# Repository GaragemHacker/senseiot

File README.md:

senseiot
========

.

Sense IoT é um projeto para pesquisa e desenvolvimento de uma rede de sensores sem fio.

Sensores
--------

* **ht**: Umidade e temperatura.
* **sound**: Som.
* **presence**: Presença.
* **gas**: Gás.
* **rain**: Chuva.

ESP8266
-------

Vamos utilizar o ESP8266 neste projeto.
Veja o wiki para uma introdução ao
[ESP8266](https://github.com/Garagem-Hacker/senseiot/wiki).

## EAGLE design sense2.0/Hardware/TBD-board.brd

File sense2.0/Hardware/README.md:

senseiot
========

Placas de Monitoramento de Consumo e Comando.

Schematic
-------
***CurrentMeasBoard**

***RelesBoard**

Board
-----

***CurrentMeasBoard**

***RelesBoard**

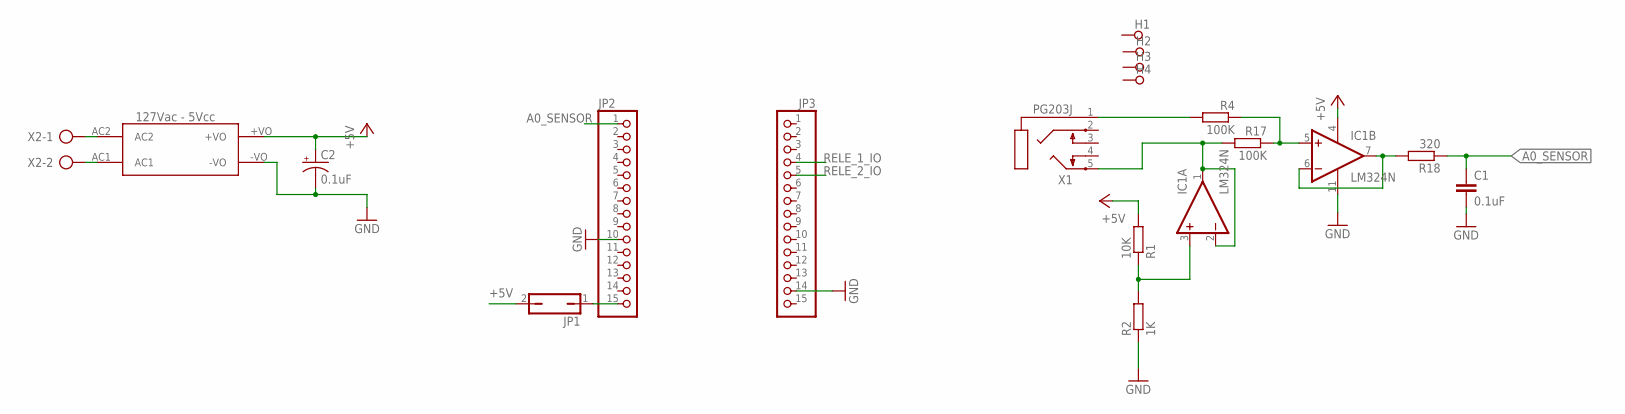
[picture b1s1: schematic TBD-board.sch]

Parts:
C1: 0.1uF; C5B5
C2: 0.1uF; E2,5-6
FONTE: HLK-PM01
H1, H2, H3, H4: SPECIAL_DRILL_0.1000; PAD_0.1000
IC1: LM324N; DIL14
JP1: JP1Q; JP1
JP2, JP3: PINHD-1X15; 1X15
R1: 10K; 0207/7
R2: 1K; 0207/7
R4, R17: 100K; 0207/7
R18: 320; 0207/7
X1: PG203J
X2: AK300/2

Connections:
+5V: C2.+, FONTE.+VO, IC1.4 (V+), JP1.2, R1.2
A0_SENSOR: C1.1, JP2.1, R18.1
GND: C1.2, C2.-, FONTE.-VO, IC1.11 (V-), JP2.10, JP3.14, R2.1
LOAD+: FONTE.AC2, X2.1
LOAD-: FONTE.AC1, X2.2
unnamed: IC1.3 (+IN), R1.1, R2.2
unnamed: JP1.1, JP2.15
unnamed: R4.2, X1.1
unnamed: IC1.5 (+IN), R4.1, R17.1
unnamed: IC1.6 (-IN), IC1.7 (OUT), R18.2
RELE_1_IO: JP3.4
RELE_2_IO: JP3.5
SENSOR-A-2: IC1.1 (OUT), IC1.2 (-IN), R17.2, X1.5

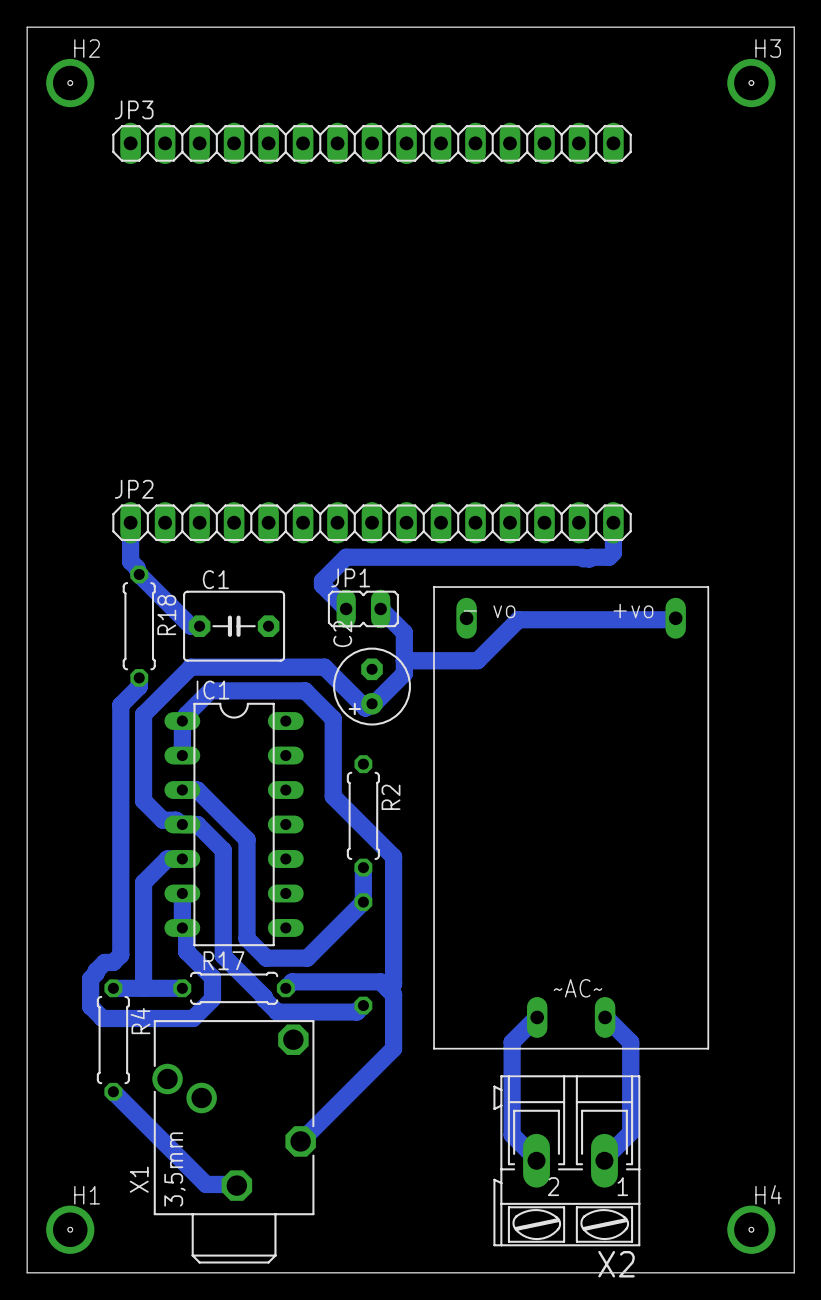
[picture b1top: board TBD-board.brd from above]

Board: 2 copper layers, 56.5 x 91.7 mm, 18 parts (1 on the bottom side), 11 nets.

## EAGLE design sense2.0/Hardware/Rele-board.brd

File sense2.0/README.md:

Senseiot 2.0
============
Nova Versão de Sense IoT

.

Sense IoT é um projeto para pesquisa e desenvolvimento de uma rede de sensores sem fio.

Hardware
--------
* **ESP8266**: Nó IoT;
* **Raspberry**: Gateway IoT;
* **ht05**: Sensor de Umidade e Temperatura;
* **sct**: Sensor de Corrente Elétrica;
* **ASQ/Ctrl-Board**: Aquisição de corrente e Comandos elétricos.
* NodeMCU: Nó Lora com sensores BMP085 e TSL2561.

Software
--------
* **API**: Da acesso do banco de dados ao Servidor Mathematica
* **Crypto**: Encript/Decrypt Payload
* **Docker**: Docker Containers
* **Mathematica**: Computer Algebra System (CAS) para Analytics dos dados
* **WebPage**: Visualização dos dados coletados e comandos para controle.

Ferramentas
-----------
* **BrokerMQTT**: Servidor IoT MQTT
* **Flask**: Microframework para aplicação Web
* **Docker**: Docker Containers
* **Crypto**: Rotinas para Criptografar/Decriptografar dados

Estrutura MQTT
--------------
Regra de comunicação dos tópicos MQTT para os dispositivos

/*		   MQTT Topic Struct

 	    'dev/node1/current2'
		|    |     |
		|    |     |
  	device(dev)  |    variable to sub/pub 
  		or   | (led1..n,temp1...n,button1...n)
 		     |
	command(cmd) |
 		     |
	IoT device node (node1...n)

*/

 Em resumo:
* Classe dispositivos(dev) ou comandos (cmd)
* Nó IoT em Questão (node1,..n)
* Variavel de Controle/Comandos (led1, button2, temp1, ...)

Dockers Containers
------------------
* **dMosquitto**: Mosquitto MQTT
* **dFlask**: Servico Backend
...

Referências 
-----------

 * [ESP8266](https://github.com/Garagem-Hacker/senseiot/wiki) - Utilização do ESP8266;
 * [ESP8266-&-MQTT](https://github.com/edgarreis/ESP8266-MQTT-Arduino) - Utilização do MQTT no ESP8266;
 * [MQTT-Python-Web](https://douglaszuqueto.com/artigos/integrando-a-aplicacao-web-com-banco-de-dados) - Integrando a aplicação MQTT à web com banco de dados;

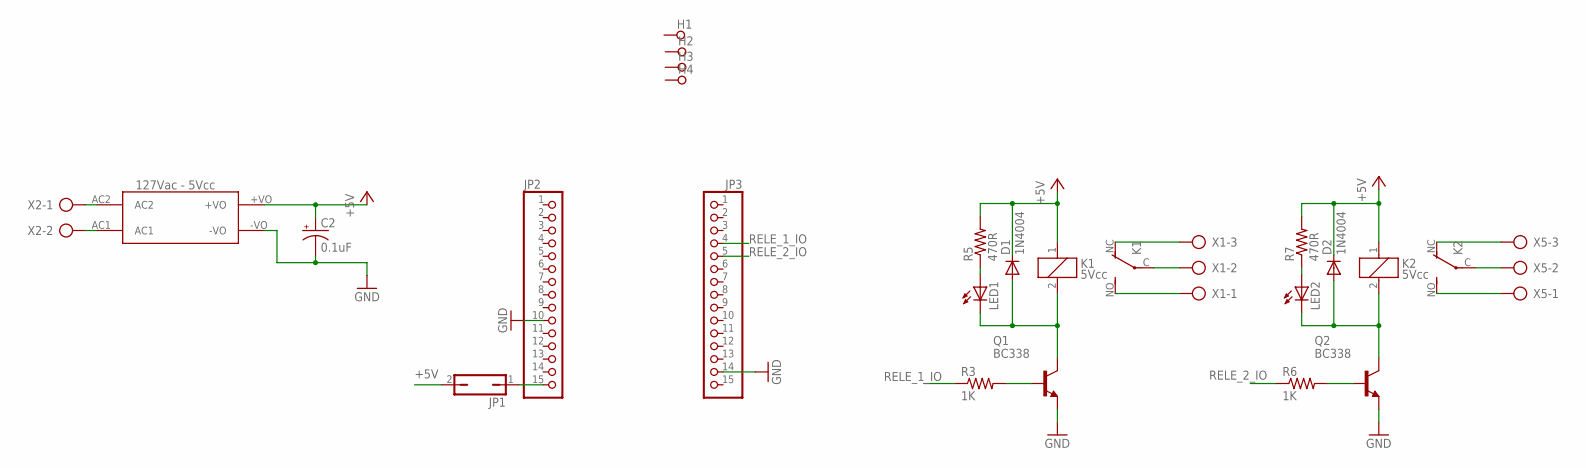
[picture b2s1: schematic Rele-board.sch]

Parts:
C2: 0.1uF; E2,5-6
D1, D2: 1N4004; DO41-10
FONTE: HLK-PM01
H1, H2, H3, H4: SPECIAL_DRILL_0.1000; PAD_0.1000
JP1: JP1Q; JP1
JP2, JP3: PINHD-1X15; 1X15
K1, K2: 5Vcc; CQ1
LED1, LED2: LED3MM
Q1, Q2: BC338; TO92-EBC
R3, R6: 1K; 0207/10
R5, R7: 470R; 0207/10
X1, X5: AK300/3
X2: AK300/2

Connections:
+5V: C2.+, D1.C, D2.C, FONTE.+VO, JP1.2, K1.1, K2.1, R5.2, R7.2
GND: C2.-, FONTE.-VO, JP2.10, JP3.14, Q1.E, Q2.E
LOAD+: FONTE.AC2, X2.1
LOAD-: FONTE.AC1, X2.2
unnamed: JP1.1, JP2.15
unnamed: K1.C, X1.2
unnamed: K1.NC (O), X1.3
unnamed: K1.NO (S), X1.1
unnamed: K2.C, X5.2
unnamed: K2.NC (O), X5.3
unnamed: K2.NO (S), X5.1
unnamed: Q2.B, R6.2
unnamed: LED2.A, R7.1
unnamed: D2.A, K2.2, LED2.K (C), Q2.C
unnamed: Q1.B, R3.2
unnamed: LED1.A, R5.1
unnamed: D1.A, K1.2, LED1.K (C), Q1.C
RELE_1_IO: JP3.4, R3.1
RELE_2_IO: JP3.5, R6.1

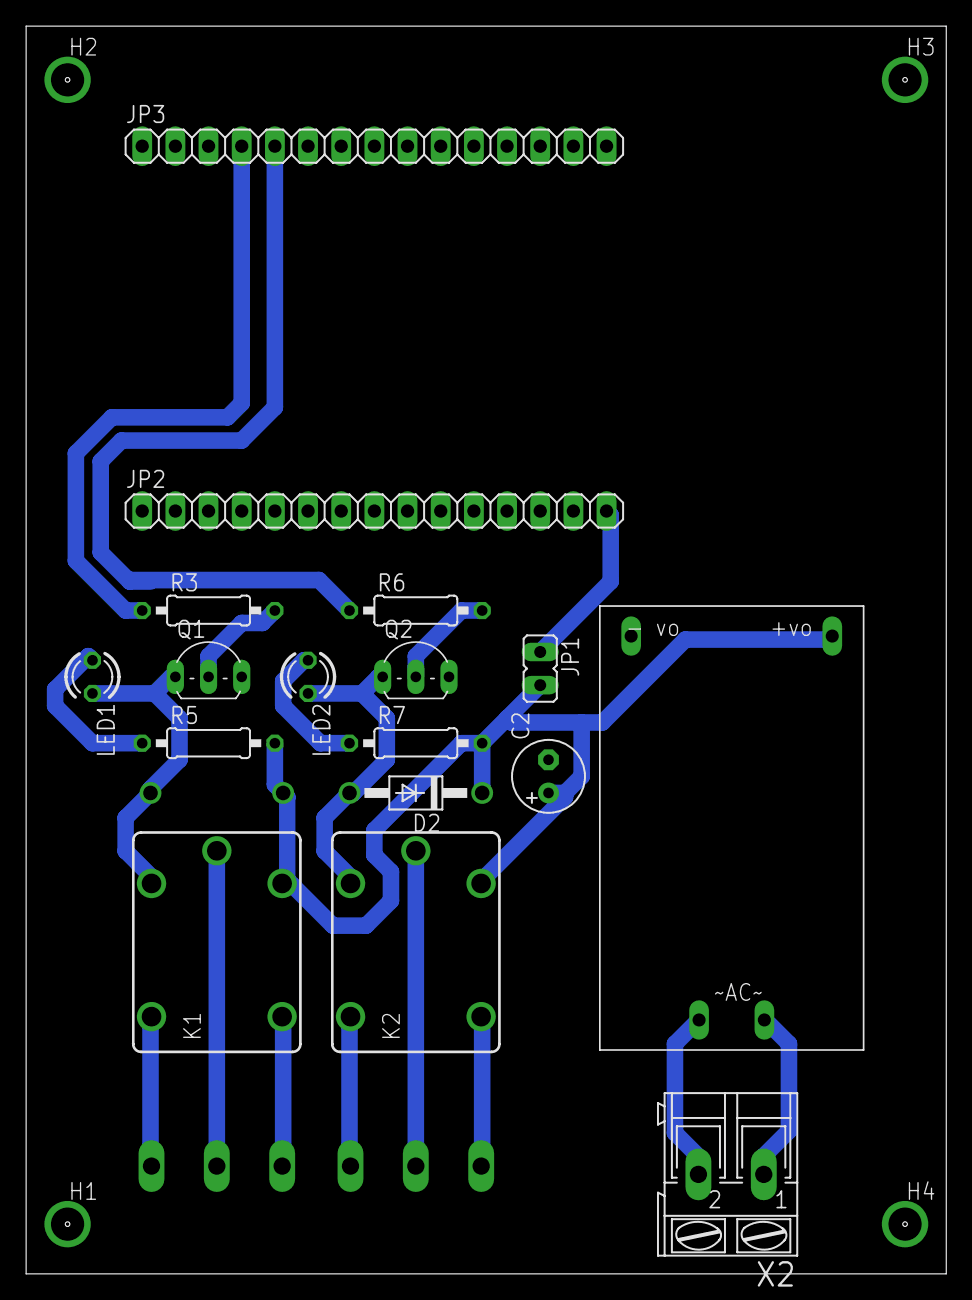
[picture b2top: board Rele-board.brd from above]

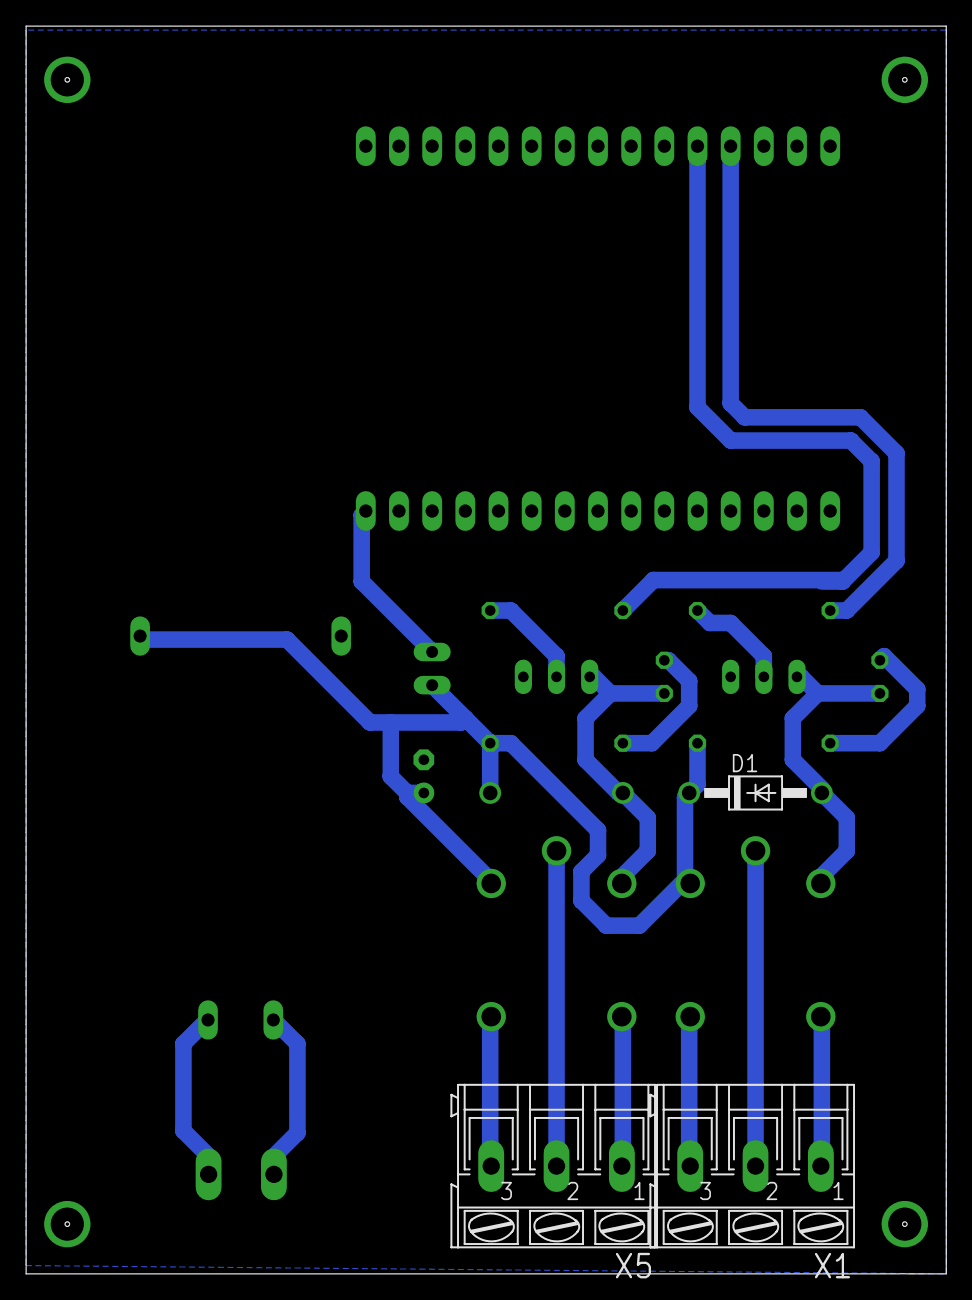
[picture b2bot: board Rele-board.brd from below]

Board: 2 copper layers, 70.5 x 95.6 mm, 24 parts (3 on the bottom side), 19 nets.

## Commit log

2015-08-29 Adiciona README.md e projeto de umidade e temperatura
2015-08-29 Adiciona logos
2015-08-29 Adiciona logo no README
2015-08-29 Adiciona logo 128x128 no README
2015-09-04 Add source code
2015-09-04 Adicionado README
2015-09-04 Adicionado hello led
2015-09-04 Adicionado codigo
2015-09-05 Adicionado imagens
2015-09-27 Add micropython led code
2015-11-18 Update wiring guide to led
2015-11-24 Versao base para o script de teste ESP+pir+NodeMCU+Lua.
2015-11-30 Melhorias no processo de utilizacao do script, agora e possivel salvar script como init.lua que o modulo carregara automaticamente no inicio.
2015-12-02 Versão inicial do arquivo com detalhes e passo-a-passo.
2015-12-02 Codigo envia um topico na mudanca de estado.
2017-08-19 Medição de Corrente de elétrica
    Medição de Correntes de no máximo 20A através da entrada analógica do ESP8266 e envio ao servidor MQTT através dos tópicos subscritos.
2017-08-22 Docker Commands
2017-08-22 Separando Pastas
2017-08-22 deleted: senseiot
2017-08-22 Moved folders
2017-08-24 Placas de Monitoramento e Comando
2017-08-27 Alterado tópicos e payload
2017-08-27 Alterado tópico
2017-08-27 Alterado tópicos
2017-08-27 As built
2017-09-04 Create API
2017-09-04 Create Dockerfile
2017-09-29 Traducao de alguns termos e breve descricao de alguns itens.
2017-10-05 Inserido tópicos e currentrms
2017-10-14 API1.0 de ponta a ponta MQTT-SQLITE-API
2017-10-14 Adicionado OTA
2017-10-14 Adiciona OTA
2017-10-14 Importação dos Dados pela API (INSTANTÂNEO)
    Adicionado Classificação e Treinamento;
    Dados Pré Processados Normal e Anormal;
    Importação dos Dados pela API (INSTANTÂNEO)
2017-10-28 Adicionado Descritivo dos programas
2017-10-28 Descritivo das funcionalidades do site
    .
2017-10-28 Adicionado Referencias
2017-11-01 Adicionando WIP da aplicacao Lora para envio de dados dos sensore BMP085 e TSL2561.
2017-11-01 Nova descricao do hardware.
2018-07-05 Pushing the senseiot studycase used on presentation on IEP
